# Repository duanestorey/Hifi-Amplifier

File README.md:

# Hifi-Amplifier
A Custom 5.1 LM3886 Based Custom Amplifier.  The LM3886 has a somewhat mythical status ever since a $3,000 gaincard was released in 1999.  It had amazing sound quality, but inside was only a tweaked LM3886 Texas Instrument 68W amplifier IC.  Since then, an entire community has evolved around these 'gainclones', which truly are hi-fidelity.  This project uses 5 of these, along with a Dolby Decoder IC, to create a complete DIY hi-fidelity 5.1 system.

A breakdown of the directory structure is as follows:

* PCBs - Each of the required PCBs in detail
* Code/ESP32 - The main amplifier code, written to run on an ESP32 WROOM 32 processor  - currently a work in progress and incomplete as the code has recently been changed from a STM32

# Design Philosophy

## PCBs

After iterations over several months to determine PCB usefulness and sizes, most PCBs now utilize a 55mmx55mm size.  This is under the minimum of 100mmx100mm low-cost options 
at several of the large-scale PCB manufacturing sites, and allows useful stacking of PCBs within the chassis.

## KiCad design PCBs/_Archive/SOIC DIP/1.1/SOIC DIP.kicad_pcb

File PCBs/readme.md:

# The completed PCBs for the amplifier

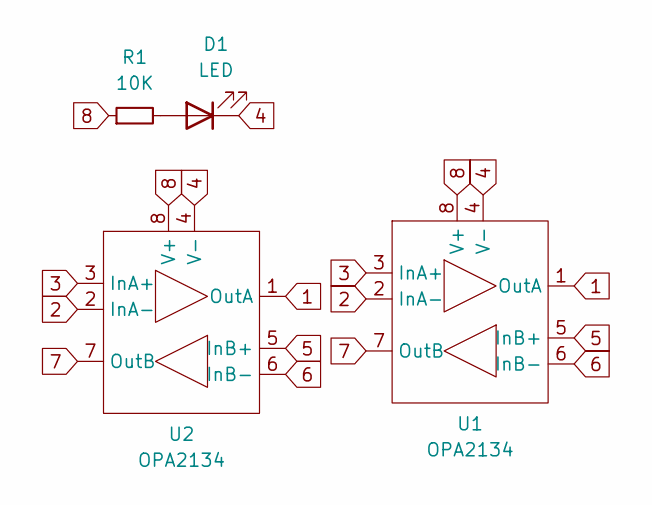
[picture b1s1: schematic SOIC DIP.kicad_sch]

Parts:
D1: LED; R_0603_1608Metric
R1: 10K; R_0603_1608Metric
U1: OPA2134; DIP-8_W7.62mm_Socket
U2: OPA2134; SOIC-8_3.9x4.9mm_P1.27mm

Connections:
1: U1.1 (OutA), U2.1 (OutA)
2: U1.2 (InA-), U2.2 (InA-)
3: U1.3 (InA+), U2.3 (InA+)
4: D1.1 (K), U1.4 (V-), U2.4 (V-)
5: U1.5 (InB+), U2.5 (InB+)
6: U1.6 (InB-), U2.6 (InB-)
7: U1.7 (OutB), U2.7 (OutB)
8: R1.1, U1.8 (V+), U2.8 (V+)
unnamed: D1.2 (A), R1.2

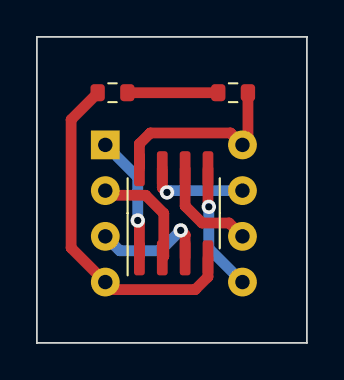
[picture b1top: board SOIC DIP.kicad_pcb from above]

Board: 2 copper layers, 15.0 x 17.0 mm, 4 parts (0 on the bottom side), 9 nets.

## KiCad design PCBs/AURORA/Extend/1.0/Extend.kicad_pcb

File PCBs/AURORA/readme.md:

## Version 2.0

### Project Style Guide

### Power Monitors

There are several INA260 power meters.  

1) MAIN Digital/Analog PSU monitor, address GND/SCL
2) MAIN Positive rail for channel amplifiers, address SCL/GND
3) 7V to 5V converter, address GND/GND
4) 7V to 3V converter, address GND/3V
5) Positive analog converter,  3V/GND
6) Entire 7V converter, 3V/3V

### Temperature Sensors

1) Microprocessor board, address GND/GND
2) Digital/Analog PSU, address GND/3V

### LED lights and resistors

The following voltages and LED colours should be used for consistency. In general, all LEDs are set at 2ma of current are 0603 size.

#### Digital Voltages

- 3.3V - Blue, set to ~2ma using 150R 
- 5.0V - Red, set to ~2ma using 1.3K

#### Analog Voltages

* +3.3V - Yellow, set to ~2ma using 620R
* +9.5V - Yellow, set to ~2ma using 3.6K
* -9.5V - Blue, set to ~2ma using 3.3K
* +34V - Yellow, set to ~2ma using 16K
* -34V - Blue, set to ~2ma using 16K
* Positive DC - Yellow, set to 2ma
* Negative DC - Blue, set to 2ma

### Design Goals
- Switch amplifier to LM4766, 2 boards, 4 channels
    - should have a microcontrolled mute
- Design miniDSP using adau1701
- Simply power supplies - take all three from the toroidal
- Modify microprocessor to have more ADC for current monitoring, and more GPIOs using add-on
- Possibly combine subwoofer board with miniDSP post-DAC filtering
- Small signal relay for swithing between filtered from channels or not
- New SPDIF board with more inputs
- Separate DAC Board or make it a HAT

#### Microprocessor

- TODO: Add connector for IR diode [IR Receiver](https://www.conrad.com/en/p/tru-components-os-0038-n-ir-receiver-non-standard-axial-lead-38-khz-5-8-mm-940-nm-35-1567234.html?srsltid=AfmBOooULA3z41DL8Pl4VzeSBMj5sArhngCSZTbEgrS--_IQduufNs6r#productDownloads)
- TODO: Add GPIO board as a HAT

#### SPDIF / DAC

- TODO: Split into separate boards, via a HAT probably
- TODO: Possibly change SPDIF connectors to screw terminals

#### SPDIF

- TODO: ADded more inputs
- TODO: Maybe add isolation transformers
- TODO: Change ground plane so SPDIF ground doesn't interfere with analog DAC ground

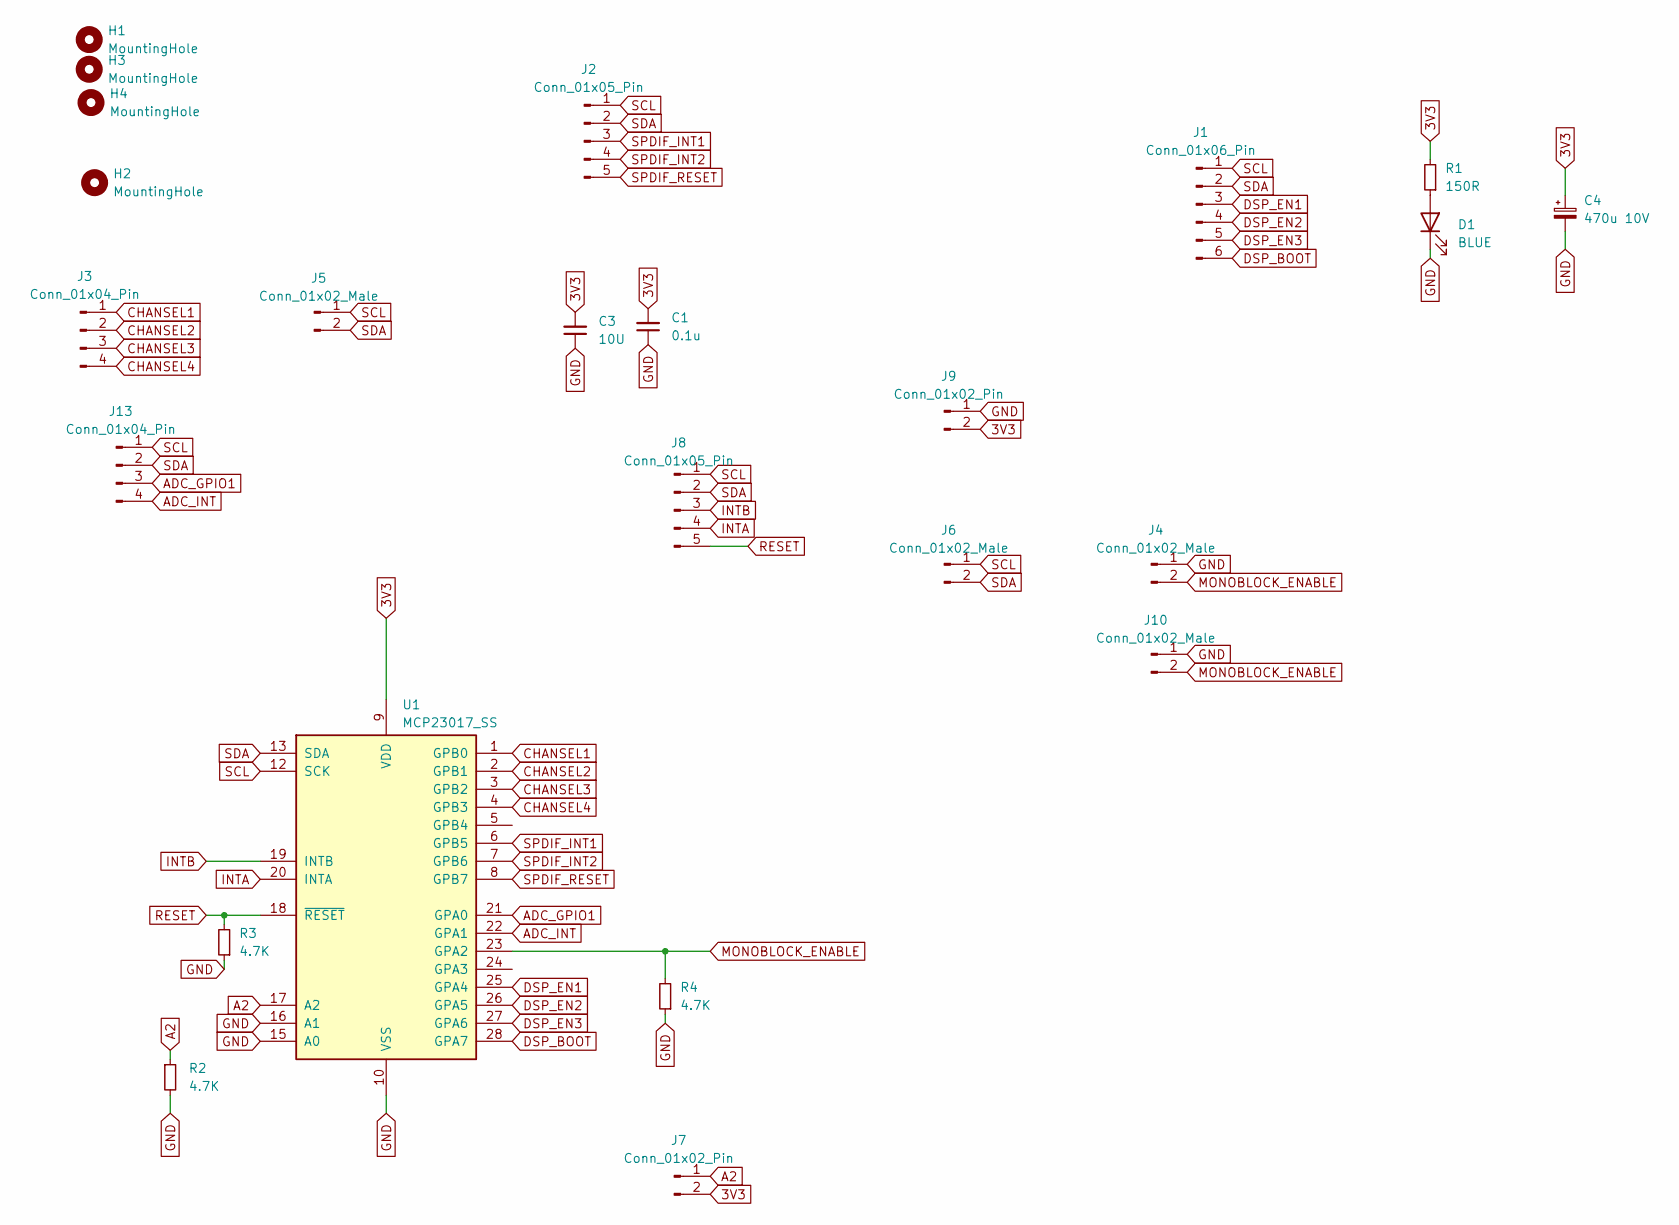
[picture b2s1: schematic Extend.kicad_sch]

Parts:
C1: 0.1u; C_0805_2012Metric_Pad1.18x1.45mm_HandSolder
C3: 10U; C_1206_3216Metric_Pad1.33x1.80mm_HandSolder
C4: 470u 10V; CP_Radial_D6.3mm_P2.50mm
D1: BLUE; LED_0603_1608Metric
H1, H2, H3, H4: MountingHole; MountingHole_3.2mm_M3_DIN965_Pad_TopOnly
J1: Conn_01x06_Pin; JST_PH_B6B-PH-K_1x06_P2.00mm_Vertical
J2, J8: Conn_01x05_Pin; JST_PH_B5B-PH-K_1x05_P2.00mm_Vertical
J3, J13: Conn_01x04_Pin; JST_PH_B4B-PH-K_1x04_P2.00mm_Vertical
J4, J5, J6, J10: Conn_01x02_Male; JST_PH_B2B-PH-K_1x02_P2.00mm_Vertical
J7: Conn_01x02_Pin; PinHeader_1x02_P2.54mm_Vertical
J9: Conn_01x02_Pin; JST_PH_B2B-PH-K_1x02_P2.00mm_Vertical
R1: 150R; R_0603_1608Metric
R2, R3, R4: 4.7K; R_0603_1608Metric_Pad0.98x0.95mm_HandSolder
U1: MCP23017_SS; SSOP-28_5.3x10.2mm_P0.65mm

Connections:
3V3: C1.2, C3.2, C4.1, J7.2, J9.2, R1.2, U1.9 (VDD)
A2: J7.1, R2.1, U1.17 (A2)
ADC_GPIO1: J13.3, U1.21 (GPA0)
ADC_INT: J13.4, U1.22 (GPA1)
CHANSEL1: J3.1, U1.1 (GPB0)
CHANSEL2: J3.2, U1.2 (GPB1)
CHANSEL3: J3.3, U1.3 (GPB2)
CHANSEL4: J3.4, U1.4 (GPB3)
DSP_BOOT: J1.6, U1.28 (GPA7)
DSP_EN1: J1.3, U1.25 (GPA4)
DSP_EN2: J1.4, U1.26 (GPA5)
DSP_EN3: J1.5, U1.27 (GPA6)
GND: C1.1, C3.1, C4.2, D1.1 (K), J4.1, J9.1, J10.1, R2.2, R3.1, R4.1, U1.10 (VSS), U1.15 (A0), U1.16 (A1)
INTA: J8.4, U1.20 (INTA)
INTB: J8.3, U1.19 (INTB)
MONOBLOCK_ENABLE: J4.2, J10.2, R4.2, U1.23 (GPA2)
unnamed: D1.2 (A), R1.1
RESET: J8.5, R3.2, U1.18 (~RESET)
SCL: J1.1, J2.1, J5.1, J6.1, J8.1, J13.1, U1.12 (SCK)
SDA: J1.2, J2.2, J5.2, J6.2, J8.2, J13.2, U1.13 (SDA)
SPDIF_INT1: J2.3, U1.6 (GPB5)
SPDIF_INT2: J2.4, U1.7 (GPB6)
SPDIF_RESET: J2.5, U1.8 (GPB7)

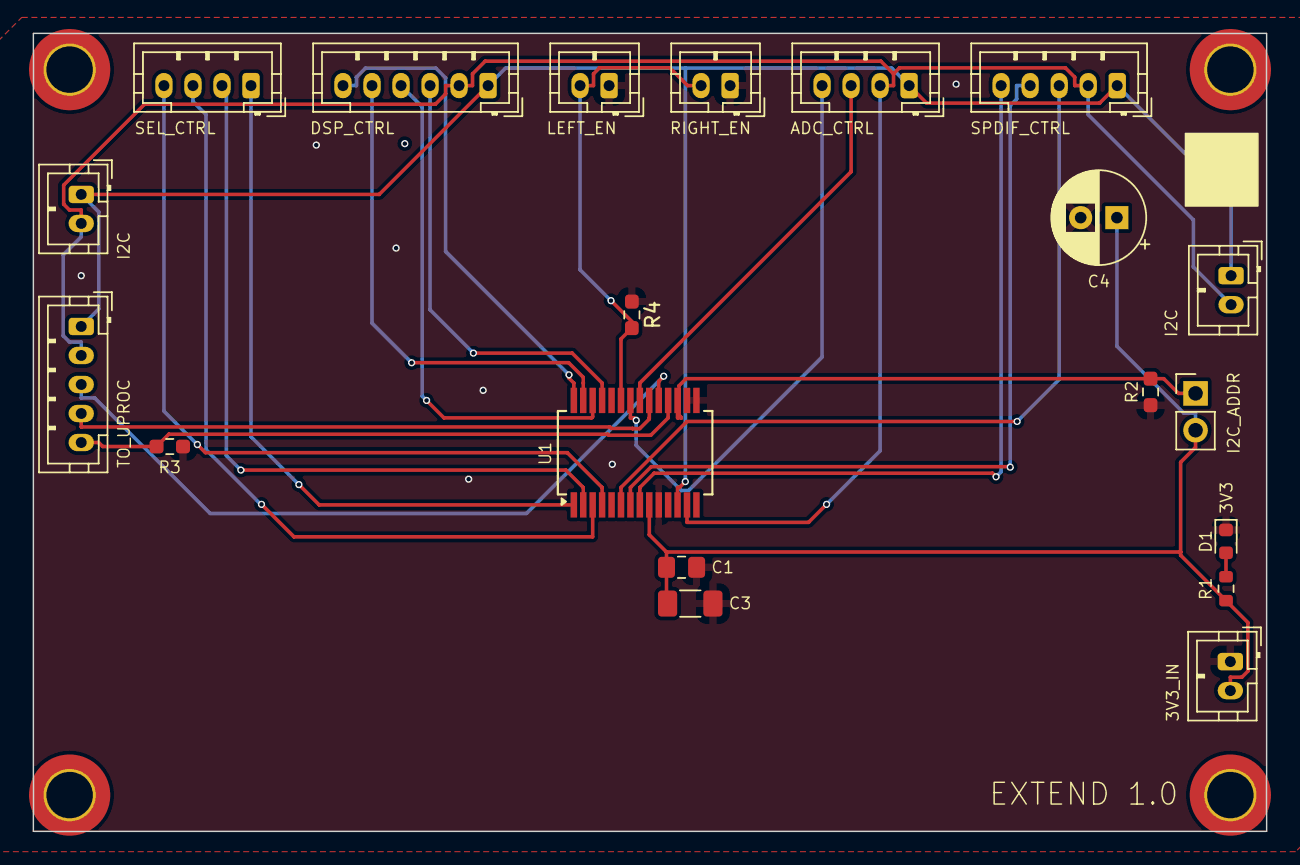
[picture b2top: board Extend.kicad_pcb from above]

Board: 2 copper layers, 85.0 x 55.0 mm, 24 parts (0 on the bottom side), 23 nets.

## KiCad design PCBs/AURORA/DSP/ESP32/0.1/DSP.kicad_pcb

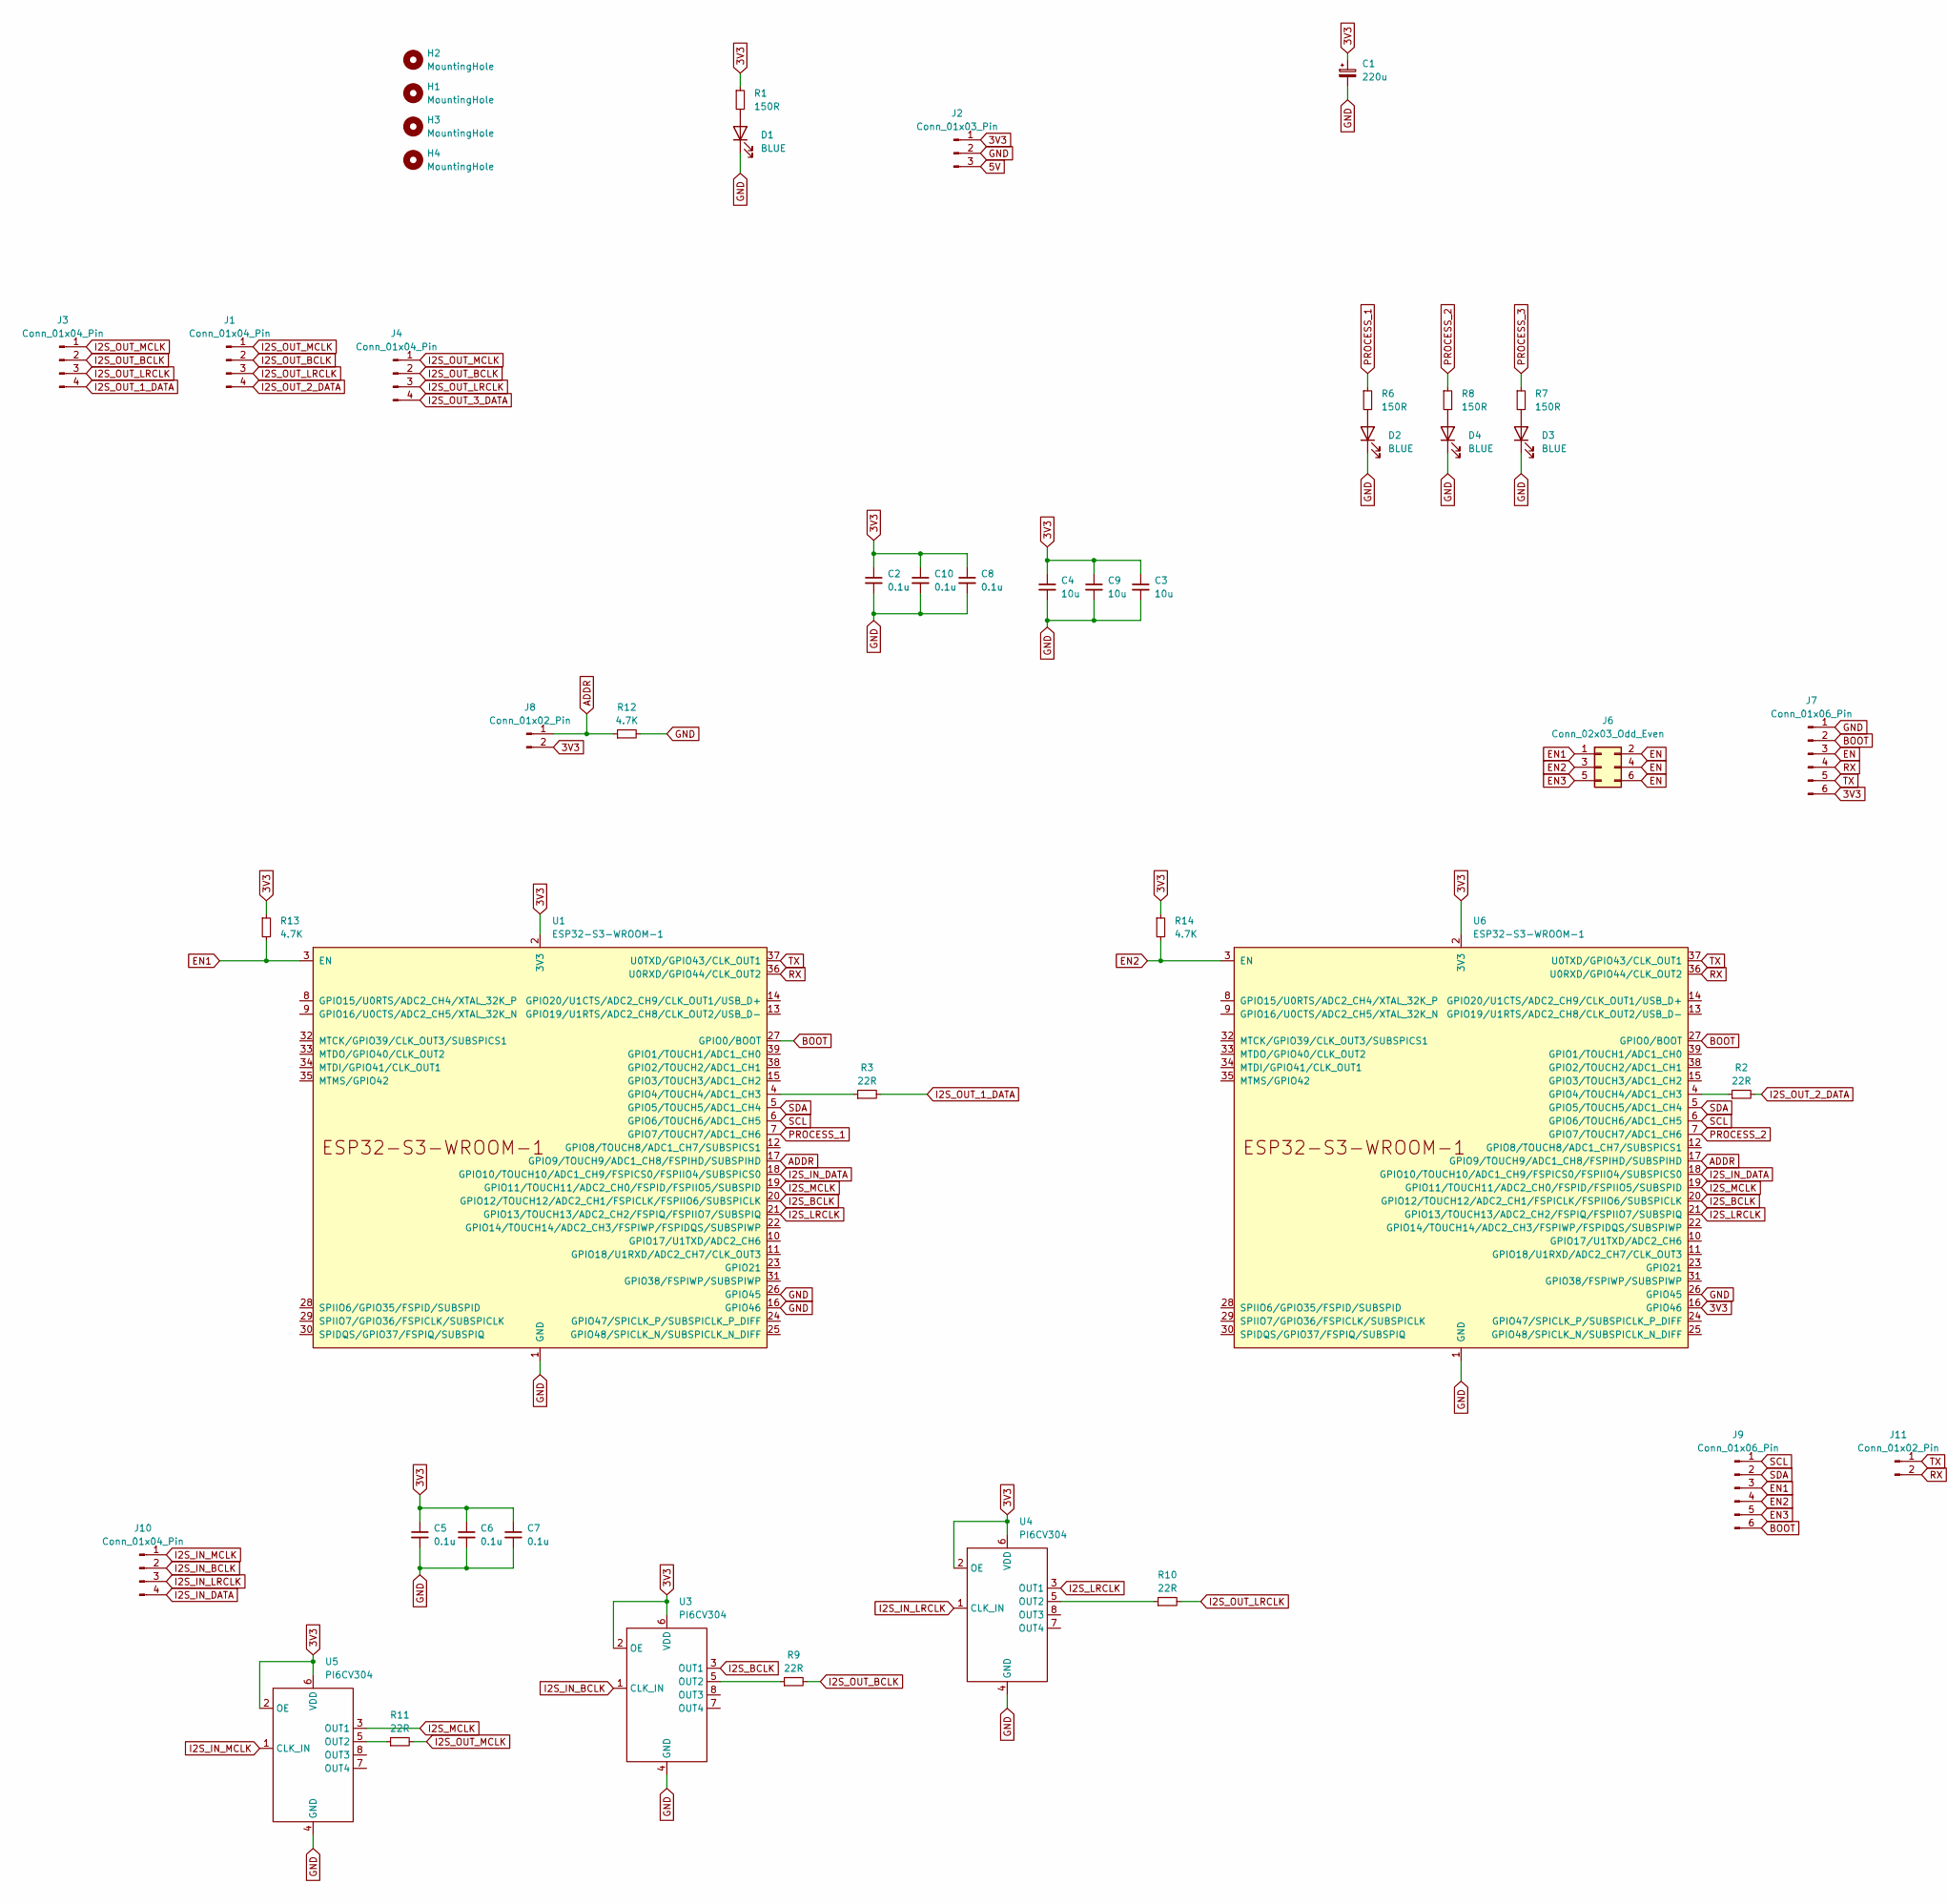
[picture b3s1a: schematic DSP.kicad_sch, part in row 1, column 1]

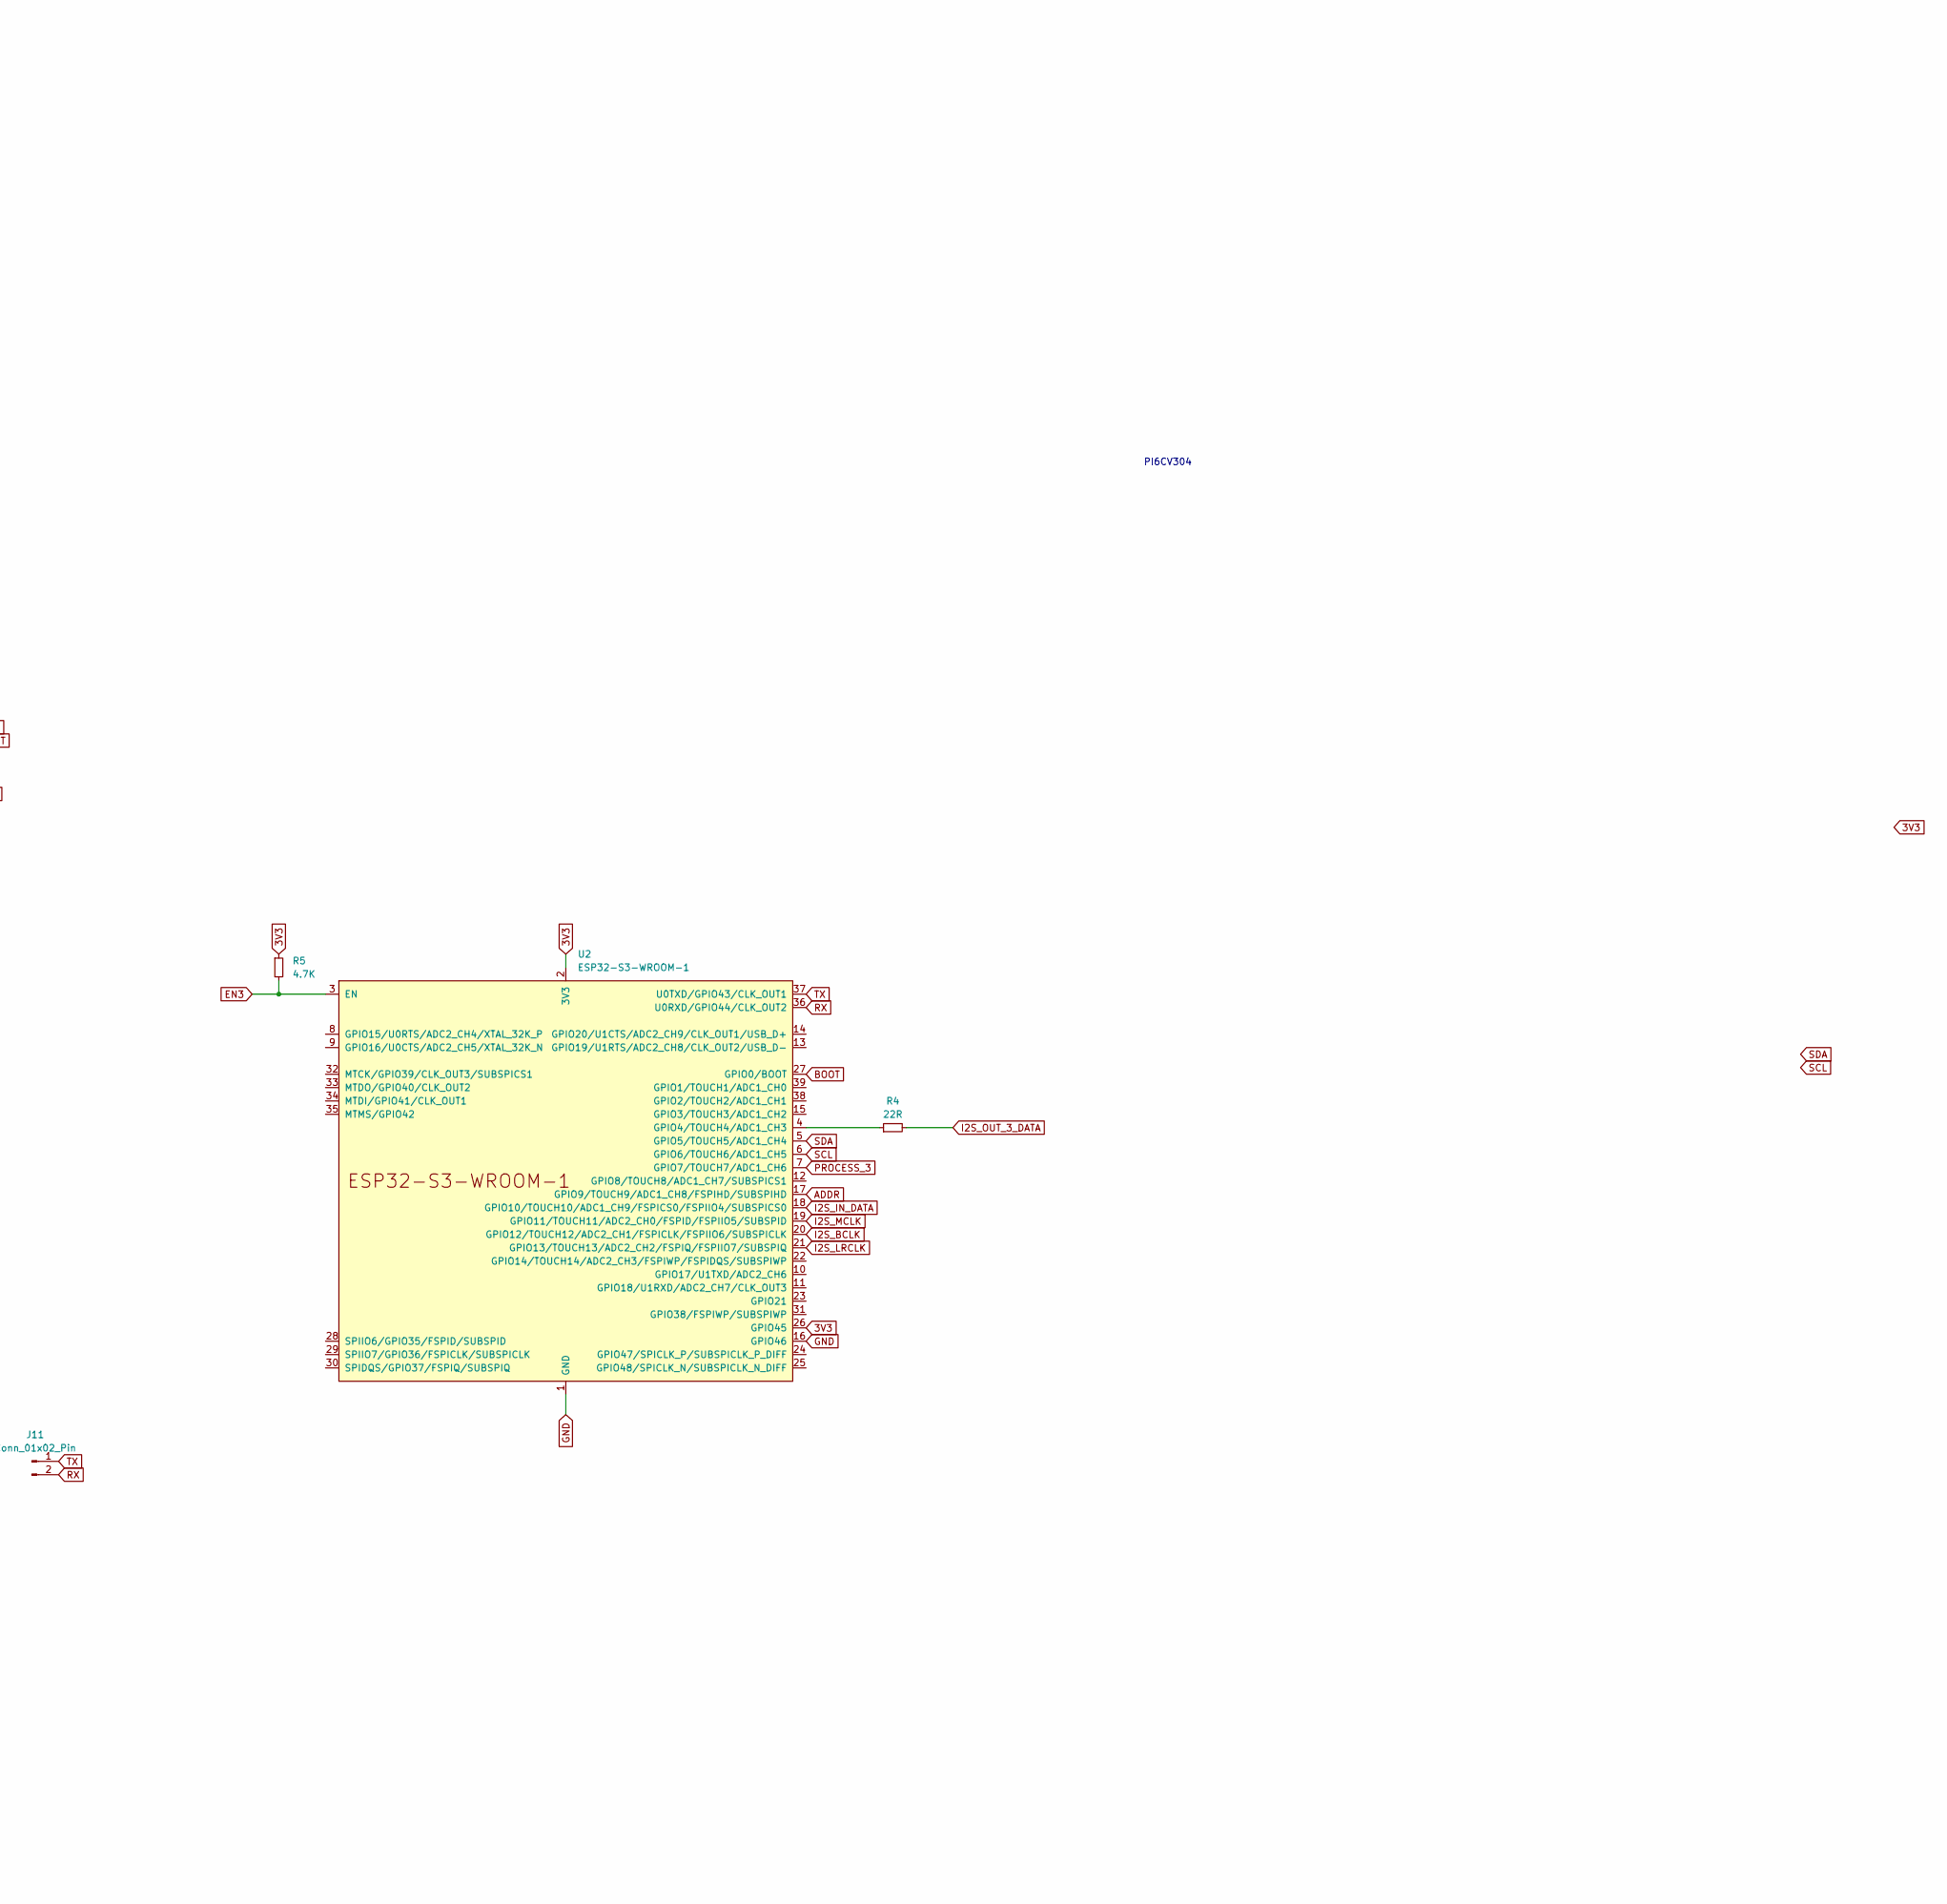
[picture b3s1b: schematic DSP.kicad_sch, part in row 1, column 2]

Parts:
C1: 220u; CP_Radial_D6.3mm_P2.50mm; LCSC C4747974
C2, C5, C6, C7, C8, C10: 0.1u; C_0603_1608Metric_Pad1.08x0.95mm_HandSolder
C3, C4, C9: 10u; C_0805_2012Metric_Pad1.18x1.45mm_HandSolder
D1, D2, D3, D4: BLUE; D_0603_1608Metric; LCSC C84259
H1, H2, H3, H4: MountingHole; MountingHole_3.2mm_M3_DIN965_Pad_TopOnly
J1, J3, J4, J10: Conn_01x04_Pin; JST_PH_B4B-PH-K_1x04_P2.00mm_Vertical
J2: Conn_01x03_Pin; JST_PH_B3B-PH-K_1x03_P2.00mm_Vertical
J6: Conn_02x03_Odd_Even; PinHeader_2x03_P2.54mm_Vertical
J7: Conn_01x06_Pin; PinHeader_1x06_P2.54mm_Vertical
J8: Conn_01x02_Pin; PinHeader_1x02_P2.54mm_Vertical
J9: Conn_01x06_Pin; JST_PH_B6B-PH-K_1x06_P2.00mm_Vertical
J11: Conn_01x02_Pin; JST_PH_B2B-PH-K_1x02_P2.00mm_Vertical
R1, R6, R7, R8: 150R; R_0603_1608Metric; LCSC C22808
R2, R3, R4, R9, R10, R11: 22R; R_0603_1608Metric
R5, R12, R13, R14: 4.7K; R_0603_1608Metric; LCSC C23162
U1, U2, U6: ESP32-S3-WROOM-1; Mouser 356-ESP32S3WRM1N16R8
U3, U4, U5: PI6CV304; TSSOP-8_4.4x3mm_P0.65mm

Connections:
3V3: C1.1, C2.1, C3.1, C4.1, C5.1, C6.1, C7.1, C8.1, C9.1, C10.1, J2.1, J7.6, J8.2, R1.1, R5.1, R13.1, R14.1, U1.2 (3V3), U2.2 (3V3), U2.26 (GPIO45), U3.2 (OE), U3.6 (VDD), U4.2 (OE), U4.6 (VDD), U5.2 (OE), U5.6 (VDD), U6.2 (3V3), U6.16 (GPIO46)
5V: J2.3
ADDR: J8.1, R12.1, U1.17 (GPIO9/TOUCH9/ADC1_CH8/FSPIHD/SUBSPIHD), U2.17 (GPIO9/TOUCH9/ADC1_CH8/FSPIHD/SUBSPIHD), U6.17 (GPIO9/TOUCH9/ADC1_CH8/FSPIHD/SUBSPIHD)
BOOT: J7.2, J9.6, U1.27 (GPIO0/BOOT), U2.27 (GPIO0/BOOT), U6.27 (GPIO0/BOOT)
EN: J6.2, J6.4, J6.6, J7.3
EN1: J6.1, J9.3, R13.2, U1.3 (EN)
EN2: J6.3, J9.4, R14.2, U6.3 (EN)
EN3: J6.5, J9.5, R5.2, U2.3 (EN)
GND: C1.2, C2.2, C3.2, C4.2, C5.2, C6.2, C7.2, C8.2, C9.2, C10.2, D1.1 (K), D2.1 (K), D3.1 (K), D4.1 (K), J2.2, J7.1, R12.2, U1.1 (GND), U1.16 (GPIO46), U1.26 (GPIO45), U1.40 (GND), U1.41 (GND), U2.1 (GND), U2.16 (GPIO46), U2.40 (GND), U2.41 (GND), U3.4 (GND), U4.4 (GND), U5.4 (GND), U6.1 (GND), U6.26 (GPIO45), U6.40 (GND), U6.41 (GND)
I2S_BCLK: U1.20 (GPIO12/TOUCH12/ADC2_CH1/FSPICLK/FSPIIO6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), U2.20 (GPIO12/TOUCH12/ADC2_CH1/FSPICLK/FSPIIO6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), U3.3 (OUT1), U6.20 (GPIO12/TOUCH12/ADC2_CH1/FSPICLK/FSPIIO6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)
I2S_IN_BCLK: J10.2, U3.1 (CLK_IN)
I2S_IN_DATA: J10.4, U1.18 (GPIO10/TOUCH10/ADC1_CH9/FSPICS0/FSPIIO4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), U2.18 (GPIO10/TOUCH10/ADC1_CH9/FSPICS0/FSPIIO4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), U6.18 (GPIO10/TOUCH10/ADC1_CH9/FSPICS0/FSPIIO4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)
I2S_IN_LRCLK: J10.3, U4.1 (CLK_IN)
I2S_IN_MCLK: J10.1, U5.1 (CLK_IN)
I2S_LRCLK: U1.21 (GPIO13/TOUCH13/ADC2_CH2/FSPIQ/FSPIIO7/S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), U2.21 (GPIO13/TOUCH13/ADC2_CH2/FSPIQ/FSPIIO7/S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), U4.3 (OUT1), U6.21 (GPIO13/TOUCH13/ADC2_CH2/FSPIQ/FSPIIO7/S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)
I2S_MCLK: U1.19 (GPIO11/TOUCH11/ADC2_CH0/FSPID/FSPIIO5/S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), U2.19 (GPIO11/TOUCH11/ADC2_CH0/FSPID/FSPIIO5/S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), U5.3 (OUT1), U6.19 (GPIO11/TOUCH11/ADC2_CH0/FSPID/FSPIIO5/S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)
I2S_OUT_1_DATA: J3.4, R3.2
I2S_OUT_2_DATA: J1.4, R2.2
I2S_OUT_3_DATA: J4.4, R4.2
I2S_OUT_BCLK: J1.2, J3.2, J4.2, R9.2
I2S_OUT_LRCLK: J1.3, J3.3, J4.3, R10.2
I2S_OUT_MCLK: J1.1, J3.1, J4.1, R11.2
unnamed: D1.2 (A), R1.2
unnamed: D2.2 (A), R6.2
unnamed: D3.2 (A), R7.2
unnamed: D4.2 (A), R8.2
unnamed: R3.1, U1.4 (GPIO4/TOUCH4/ADC1_CH3)
unnamed: R4.1, U2.4 (GPIO4/TOUCH4/ADC1_CH3)
unnamed: R9.1, U3.5 (OUT2)
unnamed: R10.1, U4.5 (OUT2)
unnamed: R11.1, U5.5 (OUT2)
unnamed: R2.1, U6.4 (GPIO4/TOUCH4/ADC1_CH3)
PROCESS_1: R6.1, U1.7 (GPIO7/TOUCH7/ADC1_CH6)
PROCESS_2: R8.1, U6.7 (GPIO7/TOUCH7/ADC1_CH6)
PROCESS_3: R7.1, U2.7 (GPIO7/TOUCH7/ADC1_CH6)
RX: J7.4, J11.2, U1.36 (U0RXD/GPIO44/CLK_OUT2), U2.36 (U0RXD/GPIO44/CLK_OUT2), U6.36 (U0RXD/GPIO44/CLK_OUT2)
SCL: J9.1, U1.6 (GPIO6/TOUCH6/ADC1_CH5), U2.6 (GPIO6/TOUCH6/ADC1_CH5), U6.6 (GPIO6/TOUCH6/ADC1_CH5)
SDA: J9.2, U1.5 (GPIO5/TOUCH5/ADC1_CH4), U2.5 (GPIO5/TOUCH5/ADC1_CH4), U6.5 (GPIO5/TOUCH5/ADC1_CH4)
TX: J7.5, J11.1, U1.37 (U0TXD/GPIO43/CLK_OUT1), U2.37 (U0TXD/GPIO43/CLK_OUT1), U6.37 (U0TXD/GPIO43/CLK_OUT1)

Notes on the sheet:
PI6CV304

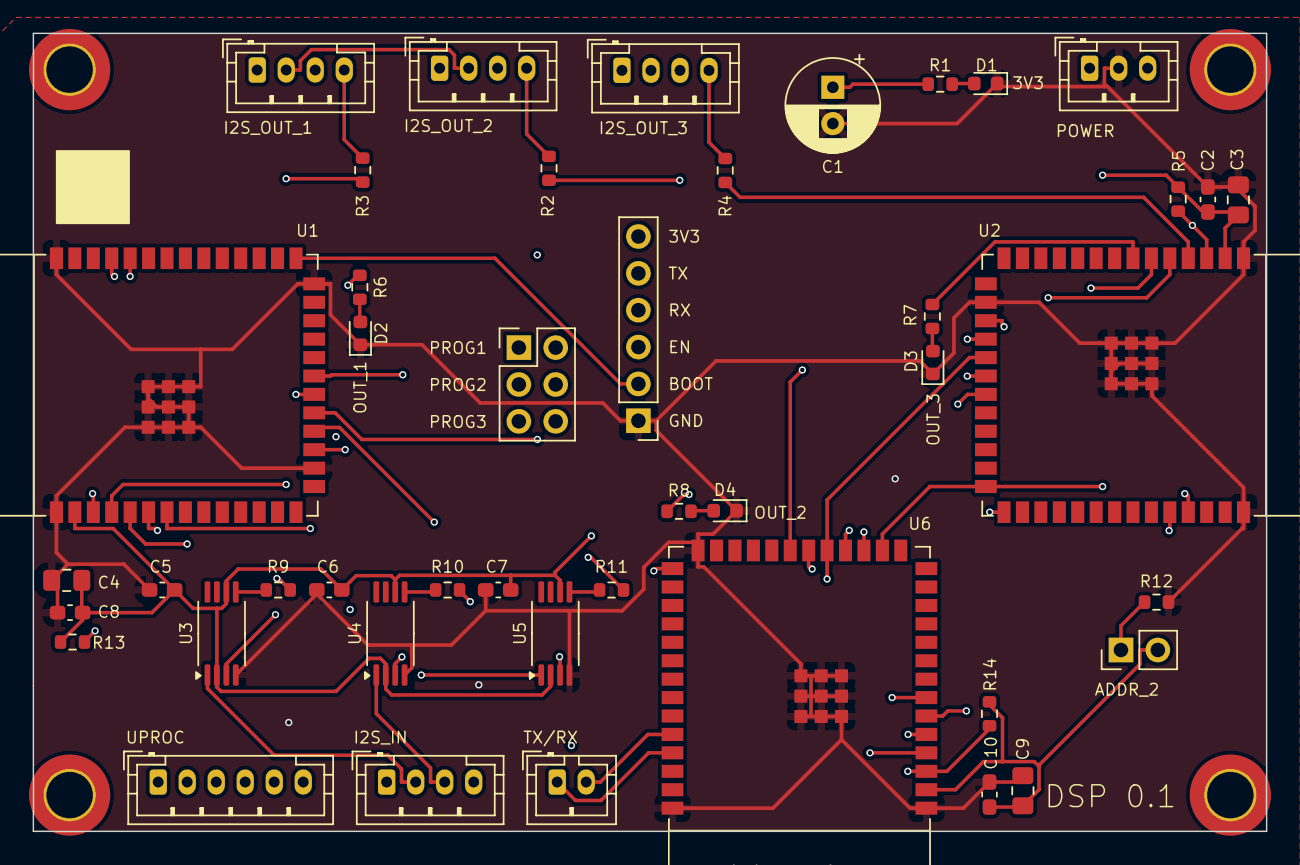
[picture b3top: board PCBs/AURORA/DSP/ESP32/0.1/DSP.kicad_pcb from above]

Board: 4 copper layers, 85.0 x 55.0 mm, 48 parts (0 on the bottom side), 38 nets.
